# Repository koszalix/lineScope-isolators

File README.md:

# lineScope isolators 

This repo contains PCB files for lineScope isolators, 
full project documentation is available [here](https://github.com/koszalix/lineScope)

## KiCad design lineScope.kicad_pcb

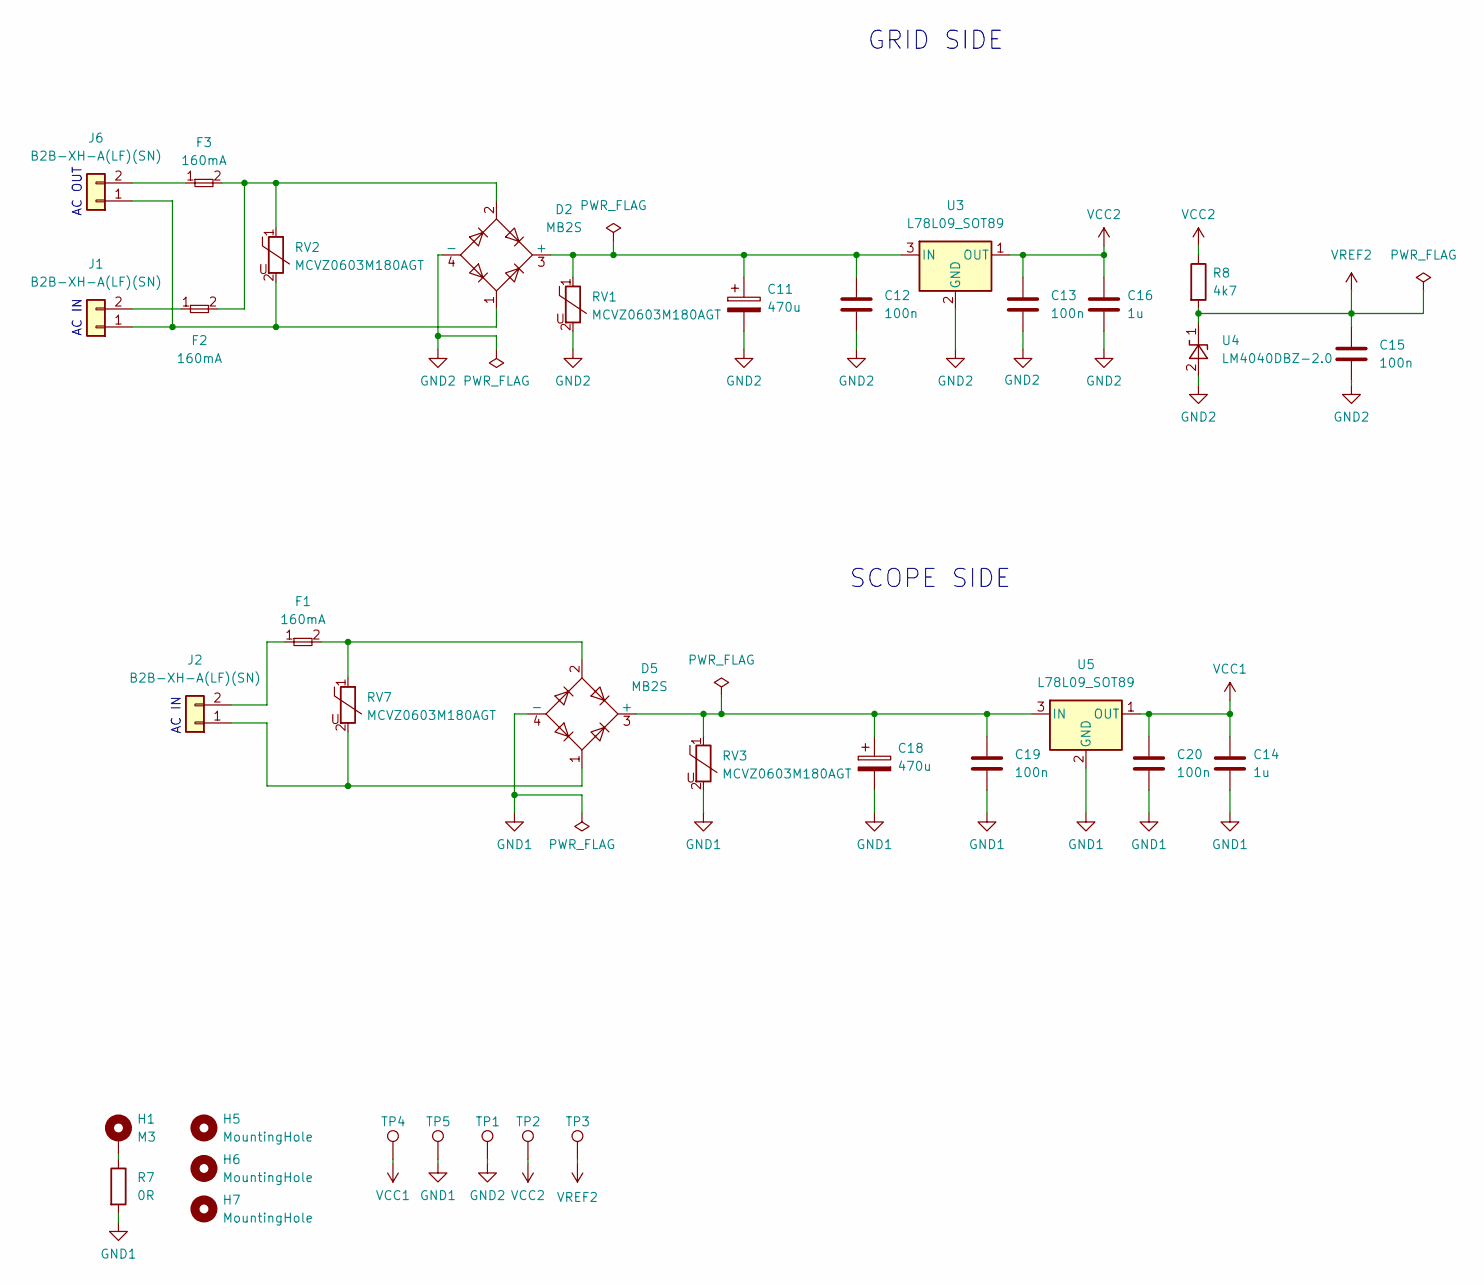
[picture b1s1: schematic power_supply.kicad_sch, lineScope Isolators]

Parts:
C11, C18: 470u; CP_Elec_10x10.5; MPN EEE1EA471P
C12, C13, C15, C19, C20: 100n; C_0603_1608Metric; Tolerance 10%; Rated voltage 50V; MPN 0603B104K500CT
C14, C16: 1u; C_0603_1608Metric; Tolerance 10%; Rated voltage 50V; MPN 0603B105K500CT
D2, D5: MB2S; TO-269AA
F1, F2, F3: 160mA; Fuse_1206_3216Metric_Pad1.42x1.75mm_HandSolder; MPN PTS120630V016
H1: M3; MountingHole_3.2mm_M3_Pad
H5, H6, H7: MountingHole; MountingHole_3.2mm_M3
J1, J2, J6: B4B-XH-A(LF)(SN); JST_XH_B2B-XH-A_1x02_P2.50mm_Vertical; MPN B2B-XH-A(LF)(SN)
R7: 0R; R_0603_1608Metric; Tolerance 1%; MPN RC0603FR-070R
R8: 4k7; R_0603_1608Metric; Tolerance 1%; MPN RC0603FR-074k7
RV1, RV2, RV3, RV7: MCVZ0603M180AGT; R_0603_1608Metric_Pad0.98x0.95mm_HandSolder; MPN MCVZ0603M180AGT
TP1, TP2, TP3, TP4, TP5: TestPoint; TestPoint_Pad_D1.0mm
U3, U5: L78L09_SOT89; SOT-89-3
U4: LM4040DBZ-2.0; SOT-23

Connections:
GND1: C14.2, C18.2, C19.2, C20.2, D5.4 (-), R7.2, RV3.2, TP5.1, U5.2 (GND); also elsewhere on the board
GND2: C11.2, C12.2, C13.2, C15.2, C16.2, D2.4 (-), RV1.2, TP1.1, U3.2 (GND), U4.2 (A); also elsewhere on the board
unnamed: C11.1, C12.1, D2.3 (+), RV1.1, U3.3 (IN)
unnamed: D2.1, J1.1, J6.1, RV2.2
unnamed: D2.2, F2.2, F3.2, RV2.1
unnamed: C18.1, C19.1, D5.3 (+), RV3.1, U5.3 (IN)
unnamed: D5.1, J2.1, RV7.2
unnamed: D5.2, F1.2, RV7.1
unnamed: F1.1, J2.2
unnamed: F2.1, J1.2
unnamed: F3.1, J6.2
unnamed: H1.1, R7.1
VCC1: C14.1, C20.1, TP4.1, U5.1 (OUT); also elsewhere on the board
VCC2: C13.1, C16.1, R8.1, TP2.1, U3.1 (OUT); also elsewhere on the board
VREF2: C15.1, R8.2, TP3.1, U4.1 (K); also elsewhere on the board

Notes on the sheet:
SCOPE SIDE
AC OUT
AC IN
GRID SIDE

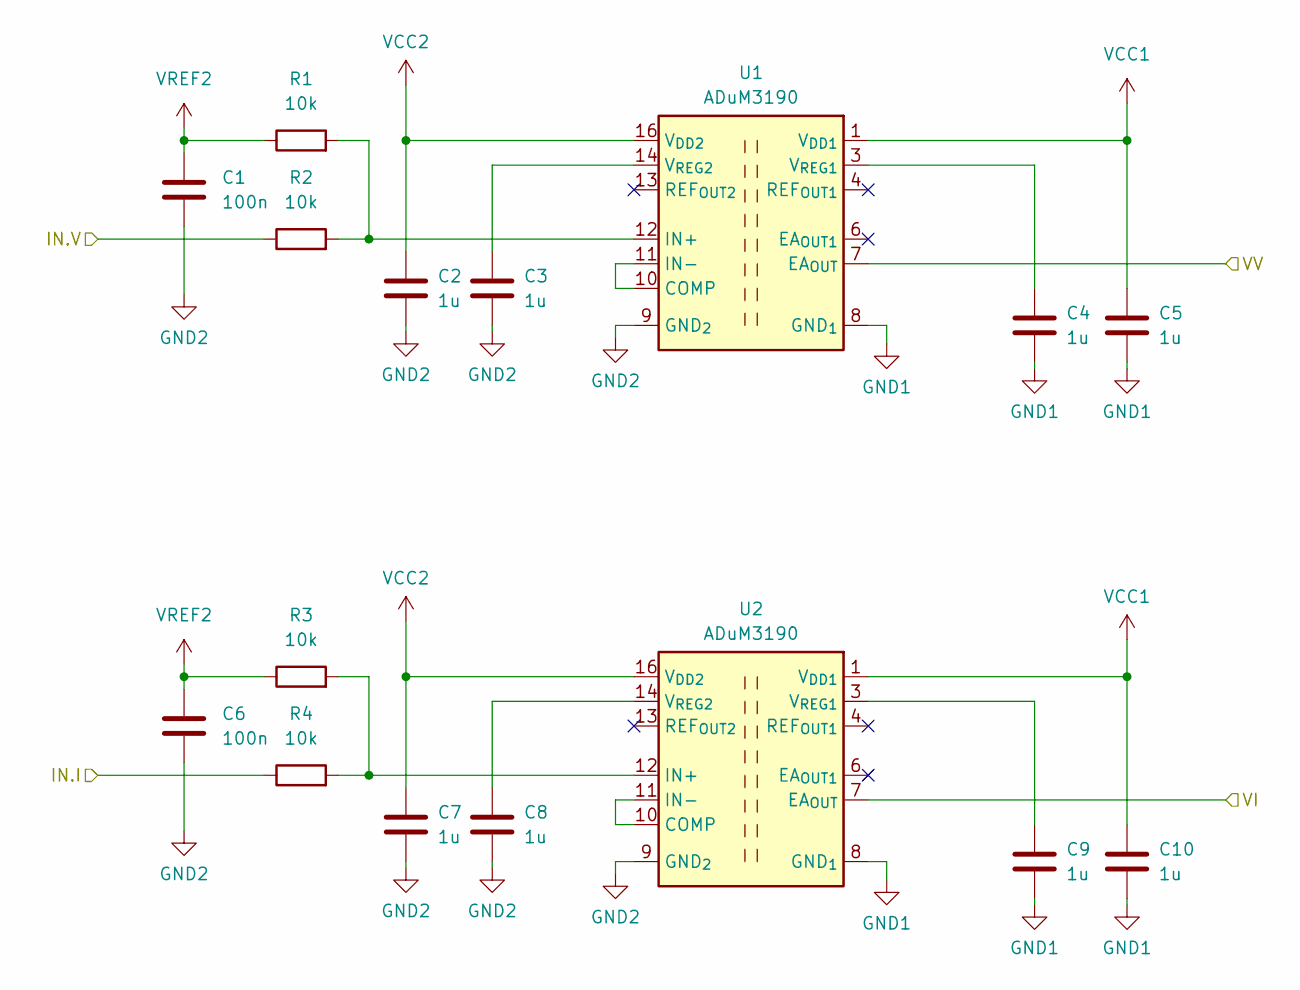
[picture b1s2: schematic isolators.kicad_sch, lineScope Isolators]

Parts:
C1, C6: 100n; C_0603_1608Metric; Tolerance 10%; Rated voltage 50V; MPN 0603B104K500CT
C2, C3, C4, C5, C7, C8, C9, C10: 1u; C_0603_1608Metric; Tolerance 10%; Rated voltage 50V; MPN 0603B105K500CT
R1, R2, R3, R4: 10k; R_0603_1608Metric; Tolerance 1%; MPN RC0603FR-0710k
U1, U2: ADuM3190; QSOP-16_3.9x4.9mm_P0.635mm; MPN ADuM3190

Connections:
/Isolators/IN.I: R4.1; also elsewhere on the board
/Isolators/IN.V: R2.1; also elsewhere on the board
/Isolators/VI: U2.7 (EA_{OUT}); also elsewhere on the board
/Isolators/VV: U1.7 (EA_{OUT}); also elsewhere on the board
GND1: C4.2, C5.2, C9.2, C10.2, U1.2 (GND_{1}), U1.8 (GND_{1}), U2.2 (GND_{1}), U2.8 (GND_{1}); also elsewhere on the board
GND2: C1.2, C2.2, C3.2, C6.2, C7.2, C8.2, U1.9 (GND_{2}), U1.15 (GND_{2}), U2.9 (GND_{2}), U2.15 (GND_{2}); also elsewhere on the board
unnamed: U1.10 (COMP), U1.11 (IN-)
unnamed: R1.2, R2.2, U1.12 (IN+)
unnamed: C4.1, U1.3 (V_{REG1})
unnamed: C3.1, U1.14 (V_{REG2})
unnamed: U2.10 (COMP), U2.11 (IN-)
unnamed: R3.2, R4.2, U2.12 (IN+)
unnamed: C9.1, U2.3 (V_{REG1})
unnamed: C8.1, U2.14 (V_{REG2})
VCC1: C5.1, C10.1, U1.1 (V_{DD1}), U2.1 (V_{DD1}); also elsewhere on the board
VCC2: C2.1, C7.1, U1.16 (V_{DD2}), U2.16 (V_{DD2}); also elsewhere on the board
VREF2: C1.1, C6.1, R1.1, R3.1; also elsewhere on the board

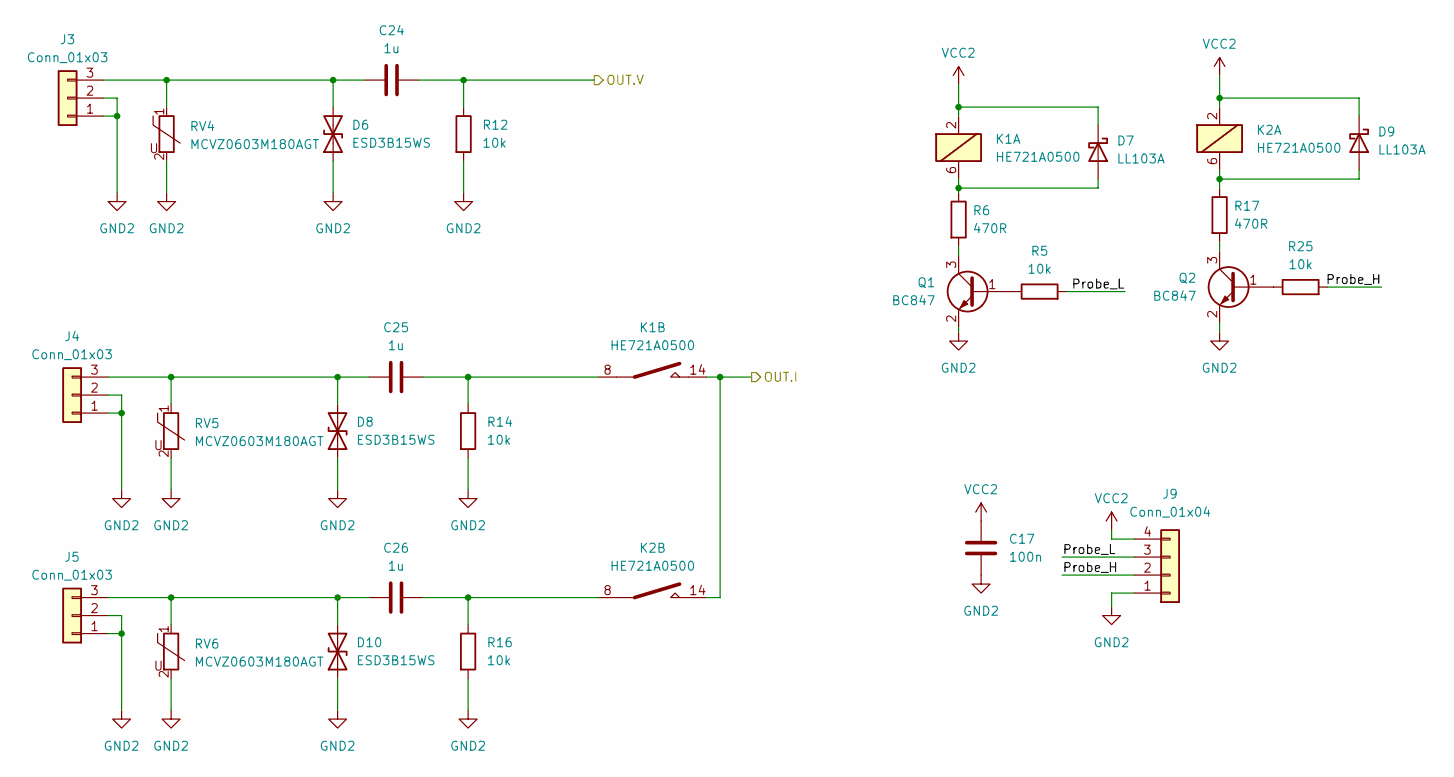
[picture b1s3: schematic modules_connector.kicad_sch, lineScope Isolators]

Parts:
C17: 100n; C_0603_1608Metric; Tolerance 10%; Rated voltage 50V; MPN 0603B104K500CT
C24, C25, C26: 1u; C_0603_1608Metric; Tolerance 10%; Rated voltage 50V; MPN 0603B105K500CT
D6, D8, D10: ESD3B15WS; D_SOD-323_HandSoldering
D7, D9: LL103A; D_MiniMELF; MPN LL103A
J3, J4, J5: Conn_01x03; PinSocket_1x03_P2.54mm_Horizontal
J9: Conn_01x04; JST_XH_B4B-XH-A_1x04_P2.50mm_Vertical
K1, K2: HE721A0500; HE721A050; MPN HE721A0500
Q1, Q2: BC847; SOT-23
R5, R12, R14, R16, R25: 10k; R_0603_1608Metric; Tolerance 1%; MPN RC0603FR-0710k
R6, R17: 470R; R_0603_1608Metric; Tolerance 1%; MPN RC0603FR-07470R
RV4, RV5, RV6: MCVZ0603M180AGT; R_0603_1608Metric_Pad0.98x0.95mm_HandSolder; MPN MCVZ0603M180AGT

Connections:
/Isolators/IN.I: K1.1, K1.14, K2.1, K2.14; also elsewhere on the board
/Isolators/IN.V: C24.2, R12.1; also elsewhere on the board
/Modules Connector/Probe_H: J9.2, R25.2
/Modules Connector/Probe_L: J9.3, R5.2
GND2: C17.2, D6.1 (A1), D8.1 (A1), D10.1 (A1), J3.1, J3.2, J4.1, J4.2, J5.1, J5.2, J9.1, Q1.2 (E), Q2.2 (E), R12.2, R14.2, R16.2, RV4.2, RV5.2, RV6.2; also elsewhere on the board
unnamed: C25.2, K1.7, K1.8, R14.1
unnamed: C26.2, K2.7, K2.8, R16.1
unnamed: C24.1, D6.2 (A2), J3.3, RV4.1
unnamed: D7.2 (A), K1.6, R6.1
unnamed: C25.1, D8.2 (A2), J4.3, RV5.1
unnamed: D9.2 (A), K2.6, R17.1
unnamed: C26.1, D10.2 (A2), J5.3, RV6.1
unnamed: Q1.1 (B), R5.1
unnamed: Q1.3 (C), R6.2
unnamed: Q2.1 (B), R25.1
unnamed: Q2.3 (C), R17.2
VCC2: C17.1, D7.1 (K), D9.1 (K), J9.4, K1.2, K2.2; also elsewhere on the board

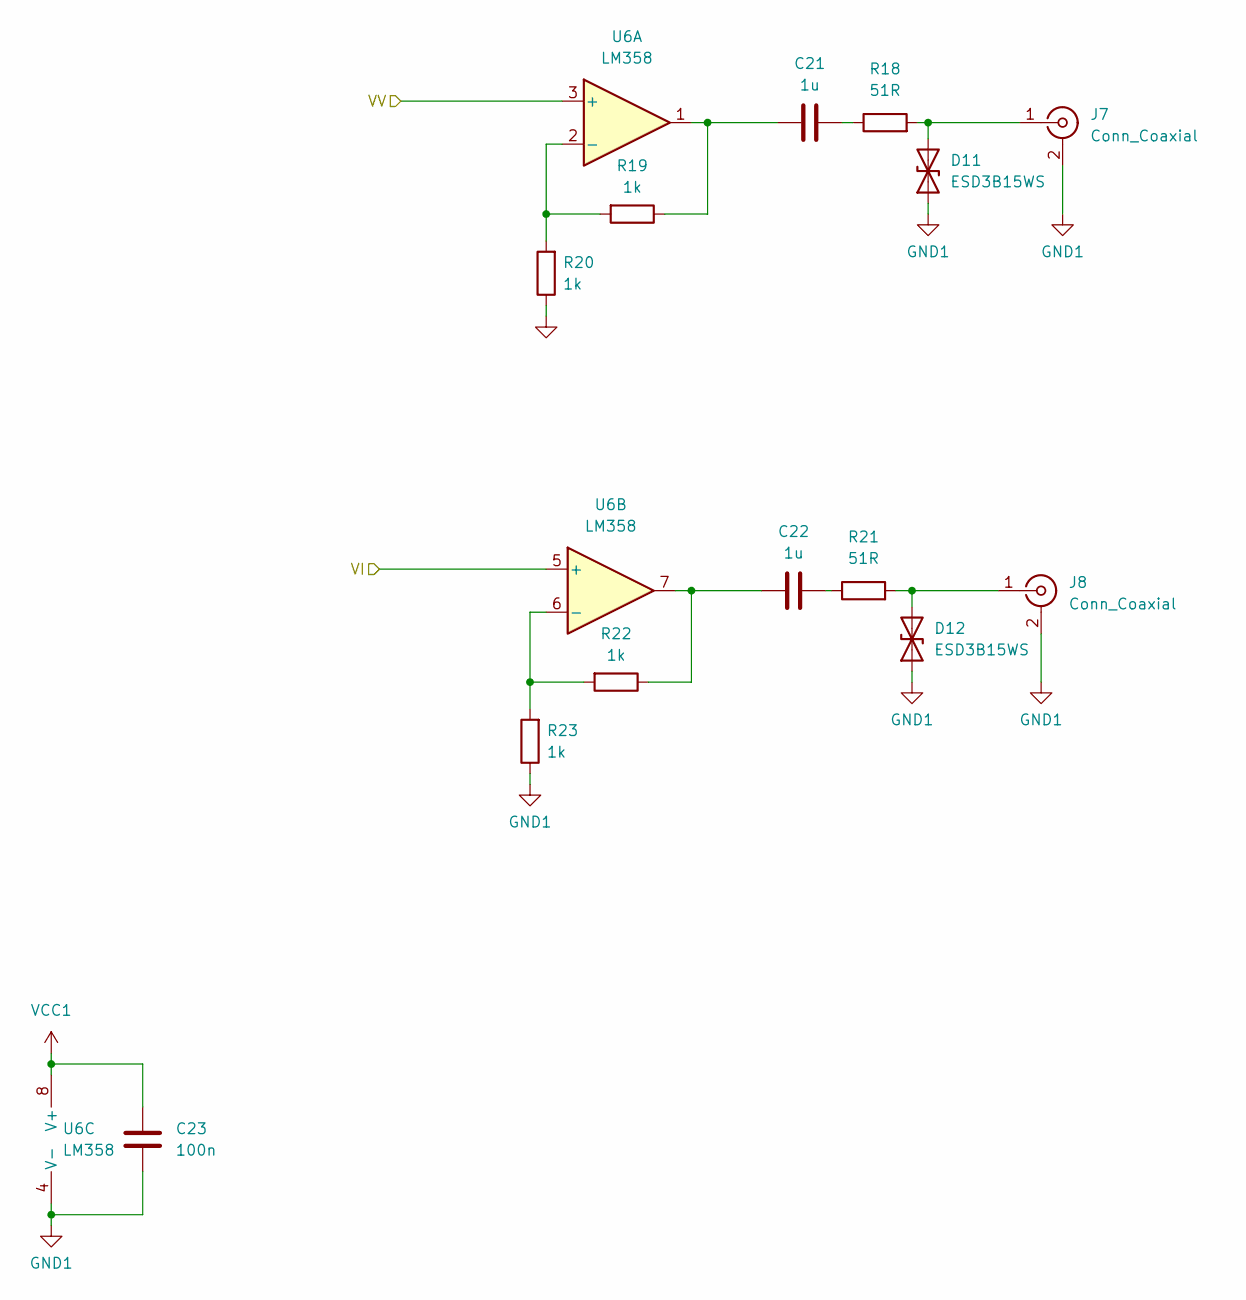
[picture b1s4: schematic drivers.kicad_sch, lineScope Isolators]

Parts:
C21, C22: 1u; C_0603_1608Metric; Tolerance 10%; Rated voltage 50V; MPN 0603B105K500CT
C23: 100n; C_0603_1608Metric; Tolerance 10%; Rated voltage 50V; MPN 0603B104K500CT
D11, D12: ESD3B15WS; D_SOD-323_HandSoldering
J7, J8: Conn_Coaxial; BNC_Amphenol_B6252HB-NPP3G-50_Horizontal
R18, R21: 51R; R_0603_1608Metric; Tolerance 1%; MPN RC0603FR-0751R
R19, R20, R22, R23: 1k; R_0603_1608Metric; Tolerance 1%; MPN RC0603FR-071k
U6: LM358; SO-8_3.9x4.9mm_P1.27mm

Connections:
/Isolators/VI: U6.5 (+); also elsewhere on the board
/Isolators/VV: U6.3 (+); also elsewhere on the board
GND1: C23.2, D11.1 (A1), D12.1 (A1), J7.2 (Ext), J8.2 (Ext), R20.1, R23.1, U6.4 (V-); also elsewhere on the board
unnamed: C21.1, R19.1, U6.1
unnamed: C21.2, R18.1
unnamed: C22.1, R22.1, U6.7
unnamed: C22.2, R21.1
unnamed: D11.2 (A2), J7.1 (In), R18.2
unnamed: D12.2 (A2), J8.1 (In), R21.2
unnamed: R19.2, R20.2, U6.2 (-)
unnamed: R22.2, R23.2, U6.6 (-)
VCC1: C23.1, U6.8 (V+); also elsewhere on the board

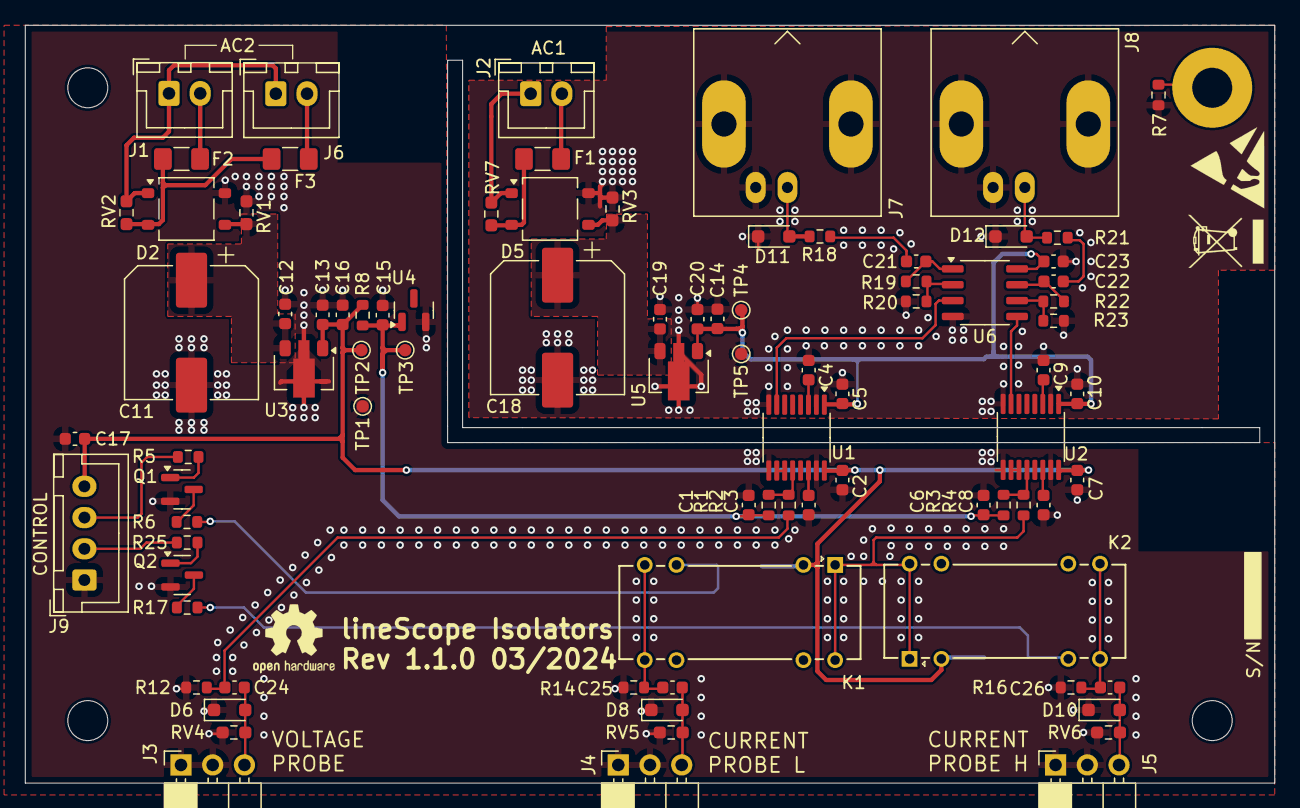
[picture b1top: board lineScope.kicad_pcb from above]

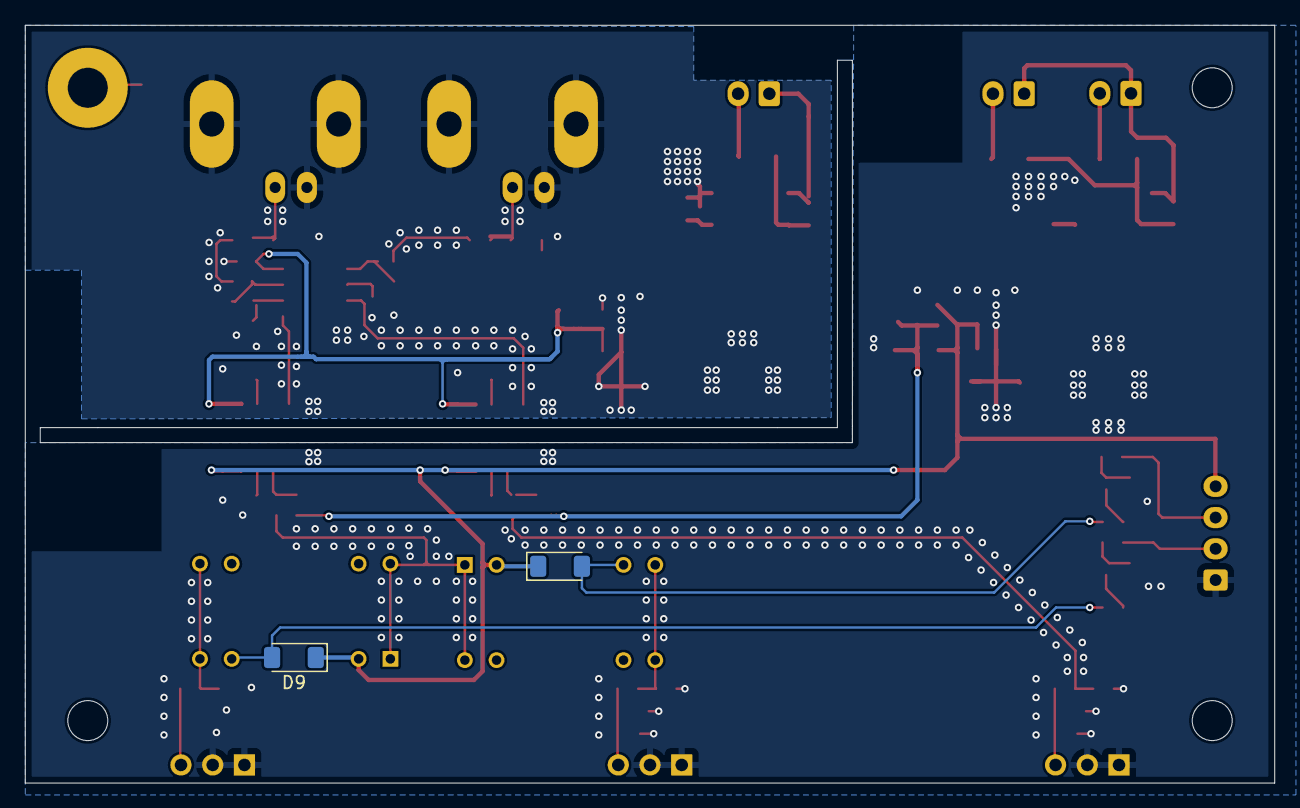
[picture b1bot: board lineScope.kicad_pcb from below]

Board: 2 copper layers, 100.0 x 60.6 mm, 92 parts (2 on the bottom side), 48 nets.

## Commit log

2024-03-20 Create schematic file
2024-03-26 Route pcb
2024-04-11 Add readme
2024-04-11 Update title frame
2024-04-21 Redesign pcb
2024-04-21 Update drc
2024-05-26 Remove DNP from R12, R14, R16
2024-05-26 Change R11, R13, R15 to 1u caps
2024-05-26 Bump revision to 1.1.0
2024-05-26 Fix C24
2024-06-05 Update git ignore
